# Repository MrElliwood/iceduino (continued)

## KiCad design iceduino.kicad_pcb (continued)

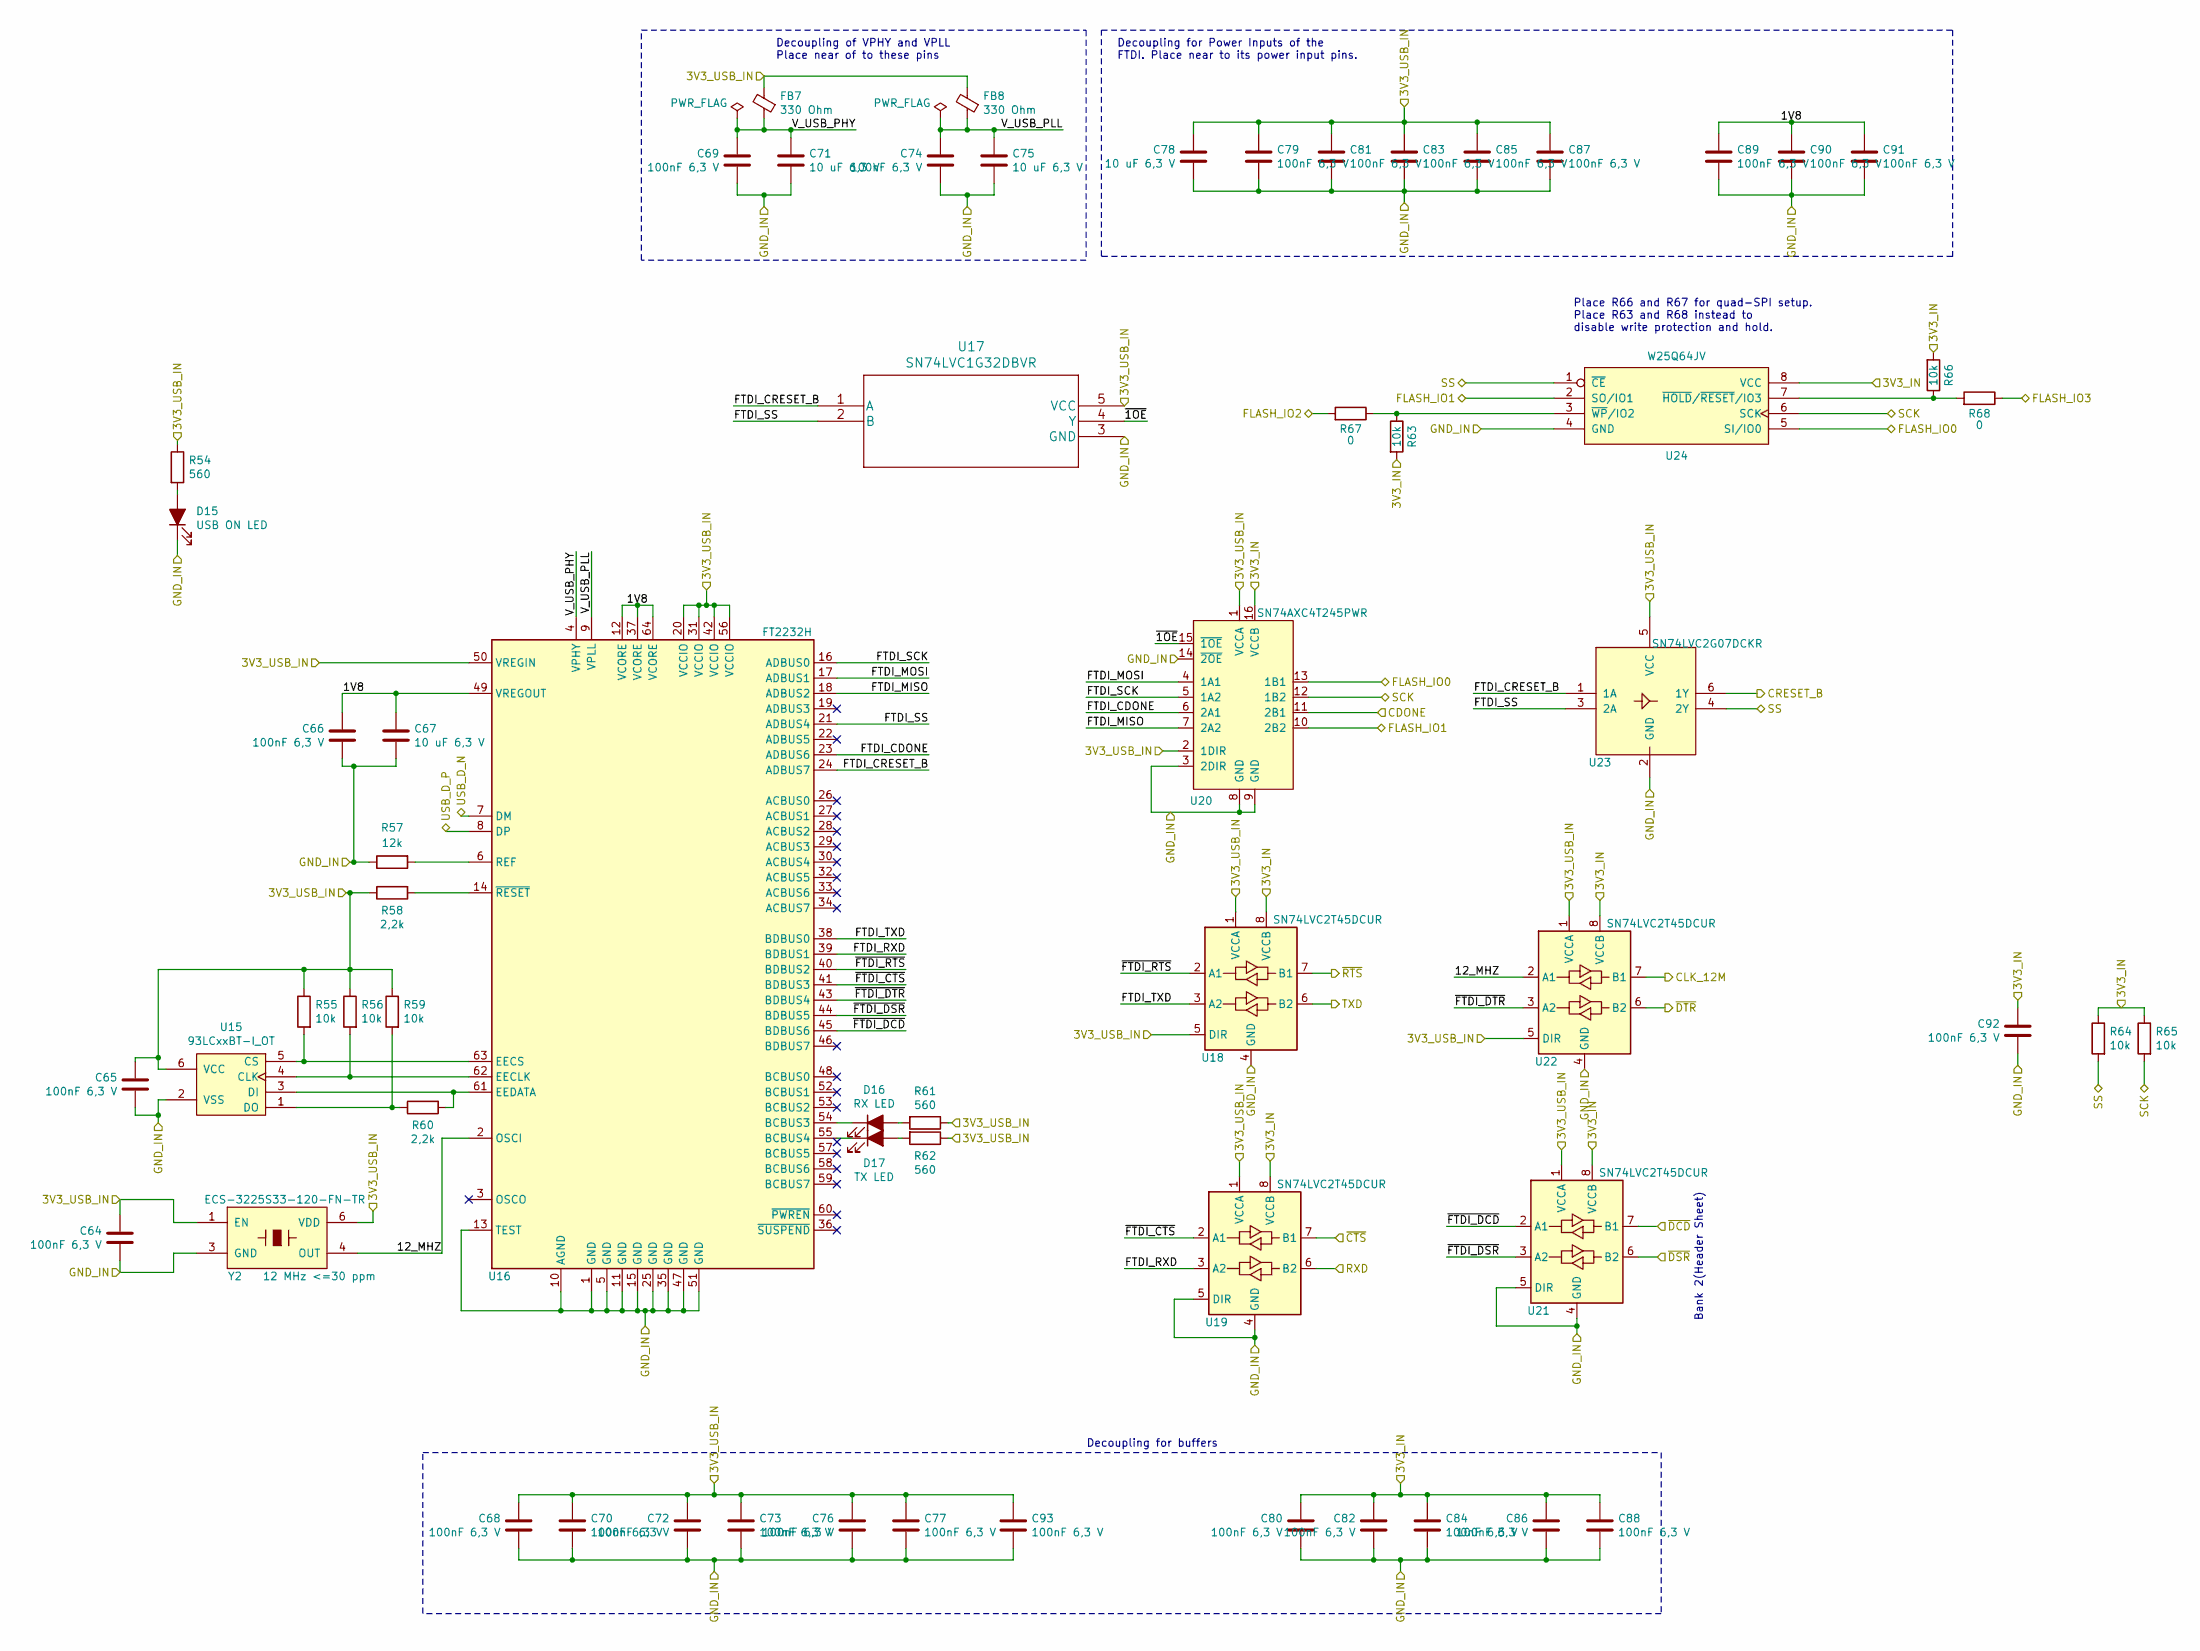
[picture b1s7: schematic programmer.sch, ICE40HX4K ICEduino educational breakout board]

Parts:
C64, C65, C66, C68, C69, C70, C72, C73, C74, C76, C77, C79, C80, C81, C82, C83, C84, C85, C86, C87, C88, C89, C90, C91, C92, C93: 100nF 6,3 V; C_0603_1608Metric; Mfg Part Num CL10B104KB8NNNC; Digikey 1276-1000-1-ND
C67, C71, C75, C78: 10 uF 6,3 V; C_0603_1608Metric; Mfg Part Num CL10A106MQ8NNNC; Digikey 1276-1119-1-ND
D15: USB ON LED; LED_0603_1608Metric; Mfg Part Num SML-D12U1WT86; Digikey SML-D12U1WT86CT-ND
D16: RX LED; LED_0603_1608Metric; Mfg Part Num SML-D12U1WT86; Digikey SML-D12U1WT86CT-ND
D17: TX LED; LED_0603_1608Metric; Mfg Part Num SML-D12U1WT86; Digikey SML-D12U1WT86CT-ND
FB7, FB8: 330 Ohm; R_0805_2012Metric; Mfg Part Num MPZ2012S331AT000; Digikey 445-1569-1-ND
R54, R61, R62: 560; R_0603_1608Metric; Mfg Part Num RK73B1JTTD561J; Digikey 2019-RK73B1JTTD561JCT-ND
R55, R56, R59, R63, R64, R65, R66: 10k; R_0603_1608Metric; Mfg Part Num RMCF0603JT10K0; Digikey RMCF0603JT10K0CT-ND
R57: 12k; R_0603_1608Metric; Mfg Part Num RC0603JR-0712KL; Digikey 311-12KGRCT-ND
R58, R60: 2,2k; R_0603_1608Metric; Mfg Part Num RC0603FR-072K2L; Digikey 311-2.20KHRCT-ND
R67, R68: 0; R_0603_1608Metric
U15: 93LCxxBT-I_OT; SOT-23-6; Mfg Part Num 93LC56BT-I/OT; Digikey 93LC56BT-I/OTCT-ND
U16: FT2232H; LQFP-64_10x10mm_P0.5mm; Mfg Part Num FT2232HL-REEL; Digikey 768-1024-1-ND
U17: SN74LVC1G32DBVR; SOT-23-5; Mfg Part Num SN74LVC1G32DBVR; Digikey 296-9847-1-ND
U18, U19, U21, U22: SN74LVC2T45DCUR; VSSOP-8_2.4x2.1mm_P0.5mm; Mfg Part Num SN74LVC2T45DCUR; Digikey 296-17014-1-ND
U20: SN74AXC4T245PWR; TSSOP-16_4.4x5mm_P0.65mm; Mfg Part Num SN74AXC4T245PWR; Digikey 296-53472-1-ND
U23: SN74LVC2G07DCKR; SOT-363_SC-70-6; Mfg Part Num SN74LVC2G07DCKR; Digikey 296-13495-1-ND
U24: W25Q64JV; SOIC-8_5.23x5.23mm_P1.27mm; Mfg Part Num W25Q64JVSSIM TR; Digikey W25Q64JVSSIMCT-ND
Y2: ECS-3225S33-120-FN-TR; Y_ECS-3225S_3.2x2.5mm_footprint; Mfg Part Num ECS-3225S33-120-FN-TR; Digikey XC2217CT-ND

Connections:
+3V3: C80.1, C82.1, C84.1, C86.1, C88.1, C92.1, R63.2, R64.1, R65.1, R66.2, U18.8 (VCCB), U19.8 (VCCB), U20.16 (VCCB), U21.8 (VCCB), U22.8 (VCCB), U24.8 (VCC); also elsewhere on the board
+3V3_FTDI: C64.1, C65.1, C68.1, C70.1, C72.1, C73.1, C76.1, C77.1, C78.1, C79.1, C81.1, C83.1, C85.1, C87.1, C93.1, FB7.2, FB8.2, R54.1, R55.1, R56.1, R58.1, R59.1, R61.1, R62.1, U15.6 (VCC), U16.20 (VCCIO), U16.31 (VCCIO), U16.42 (VCCIO), U16.50 (VREGIN), U16.56 (VCCIO), U17.5 (VCC), U18.1 (VCCA), U18.5 (DIR), U19.1 (VCCA), U20.1 (VCCA), U20.2 (1DIR), U21.1 (VCCA), U22.1 (VCCA), U22.5 (DIR), U23.5 (VCC), Y2.1 (EN), Y2.6 (VDD); also elsewhere on the board
/CDONE: U20.11 (2B1); also elsewhere on the board
/CLK_12M: U22.7 (B1); also elsewhere on the board
/CRESET_B: U23.6 (1Y); also elsewhere on the board
/FLASH_IO0: U20.13 (1B1), U24.5 (SI/IO0); also elsewhere on the board
/FLASH_IO1: U20.10 (2B2), U24.2 (SO/IO1); also elsewhere on the board
/FLASH_IO2: R67.2; also elsewhere on the board
/FLASH_IO3: R68.1; also elsewhere on the board
/RXD: U19.6 (B2); also elsewhere on the board
/SCK: R65.2, U20.12 (1B2), U24.6 (SCK); also elsewhere on the board
/SS: R64.2, U23.4 (2Y), U24.1 (~CE~); also elsewhere on the board
/TXD: U18.6 (B2); also elsewhere on the board
/USB_D_N: U16.7 (DM); also elsewhere on the board
/USB_D_P: U16.8 (DP); also elsewhere on the board
/USB_PROGRAMMER/1V8: C66.1, C67.1, C89.1, C90.1, C91.1, U16.12 (VCORE), U16.37 (VCORE), U16.49 (VREGOUT), U16.64 (VCORE)
/USB_PROGRAMMER/12_MHZ: U16.2 (OSCI), U22.2 (A1), Y2.4 (OUT)
/USB_PROGRAMMER/FTDI_CDONE: U16.23 (ADBUS6), U20.6 (2A1)
/USB_PROGRAMMER/FTDI_CRESET_B: U16.24 (ADBUS7), U17.1 (A), U23.1 (1A)
/USB_PROGRAMMER/FTDI_MISO: U16.18 (ADBUS2), U20.7 (2A2)
/USB_PROGRAMMER/FTDI_MOSI: U16.17 (ADBUS1), U20.4 (1A1)
/USB_PROGRAMMER/FTDI_RXD: U16.39 (BDBUS1), U19.3 (A2)
/USB_PROGRAMMER/FTDI_SCK: U16.16 (ADBUS0), U20.5 (1A2)
/USB_PROGRAMMER/FTDI_SS: U16.21 (ADBUS4), U17.2 (B), U23.3 (2A)
/USB_PROGRAMMER/FTDI_TXD: U16.38 (BDBUS0), U18.3 (A2)
/USB_PROGRAMMER/V_USB_PHY: C69.1, C71.1, FB7.1, U16.4 (VPHY)
/USB_PROGRAMMER/V_USB_PLL: C74.1, C75.1, FB8.1, U16.9 (VPLL)
/USB_PROGRAMMER/~1OE~: U17.4 (Y), U20.15 (~1OE~)
/USB_PROGRAMMER/~FTDI_CTS~: U16.41 (BDBUS3), U19.2 (A1)
/USB_PROGRAMMER/~FTDI_DCD~: U16.45 (BDBUS6), U21.2 (A1)
/USB_PROGRAMMER/~FTDI_DSR~: U16.44 (BDBUS5), U21.3 (A2)
/USB_PROGRAMMER/~FTDI_DTR~: U16.43 (BDBUS4), U22.3 (A2)
/USB_PROGRAMMER/~FTDI_RTS~: U16.40 (BDBUS2), U18.2 (A1)
/~CTS~: U19.7 (B1); also elsewhere on the board
/~DCD~: U21.7 (B1); also elsewhere on the board
/~DSR~: U21.6 (B2); also elsewhere on the board
/~DTR~: U22.6 (B2); also elsewhere on the board
/~RTS~: U18.7 (B1); also elsewhere on the board
GND: C64.2, C65.2, C66.2, C67.2, C68.2, C69.2, C70.2, C71.2, C72.2, C73.2, C74.2, C75.2, C76.2, C77.2, C78.2, C79.2, C80.2, C81.2, C82.2, C83.2, C84.2, C85.2, C86.2, C87.2, C88.2, C89.2, C90.2, C91.2, C92.2, C93.2, D15.1 (K), R57.1, U15.2 (VSS), U16.1 (GND), U16.5 (GND), U16.10 (AGND), U16.11 (GND), U16.13 (TEST), U16.15 (GND), U16.25 (GND), U16.35 (GND), U16.47 (GND), U16.51 (GND), U17.3 (GND), U18.4 (GND), U19.4 (GND), U19.5 (DIR), U20.3 (2DIR), U20.8 (GND), U20.9 (GND), U20.14 (~2OE~), U21.4 (GND), U21.5 (DIR), U22.4 (GND), U23.2 (GND), U24.4 (GND), Y2.3 (GND); also elsewhere on the board
unnamed: D15.2 (A), R54.2
unnamed: D16.1 (K), U16.54 (BCBUS3)
unnamed: D16.2 (A), R61.2
unnamed: D17.1 (K), U16.55 (BCBUS4)
unnamed: D17.2 (A), R62.2
unnamed: R55.2, U15.5 (CS), U16.63 (EECS)
unnamed: R56.2, U15.4 (CLK), U16.62 (EECLK)
unnamed: R57.2, U16.6 (REF)
unnamed: R58.2, U16.14 (~RESET)
unnamed: R59.2, R60.1, U15.1 (DO)
unnamed: R60.2, U15.3 (DI), U16.61 (EEDATA)
unnamed: R63.1, R67.1, U24.3 (~WP~/IO2)
unnamed: R66.1, R68.2, U24.7 (~HOLD~/~RESET~/IO3)

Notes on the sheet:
Decoupling of VPHY and VPLL Place near of to these pins
Bank 2(Header Sheet)
Decoupling for Power Inputs of the FTDI. Place near to its power input pins.
Decoupling for buffers
Place R66 and R67 for quad-SPI setup. Place R63 and R68 instead to disable write protection and hold.

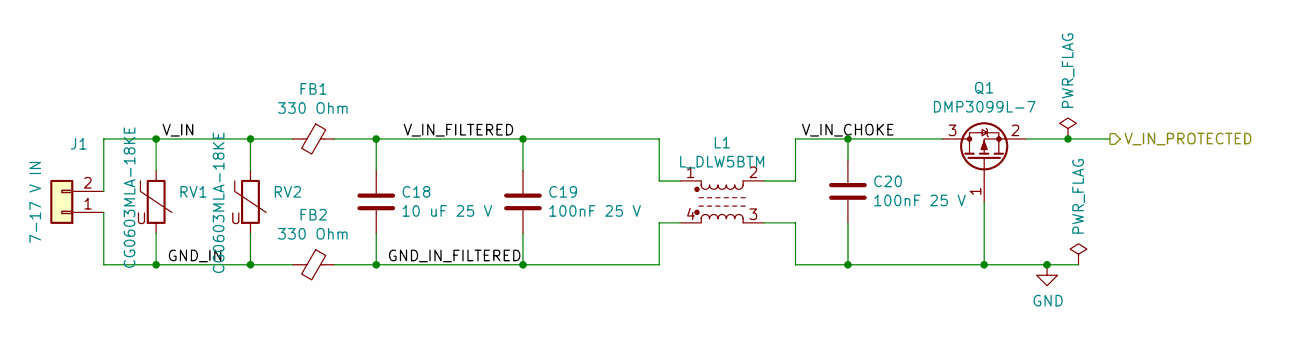
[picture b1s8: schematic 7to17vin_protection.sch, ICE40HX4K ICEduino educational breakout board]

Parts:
C18: 10 uF 25 V; C_0805_2012Metric; Mfg Part Num CL21A106KAYNNNE; Digikey 1276-2891-1-ND
C19, C20: 100nF 25 V; C_0603_1608Metric; Mfg Part Num CL10B104KB8NNNC; Digikey 1276-1000-1-ND
FB1, FB2: 330 Ohm; R_0805_2012Metric; Mfg Part Num MPZ2012S331AT000; Digikey 445-1569-1-ND
J1: 7-17 V IN; TerminalBlock_bornier-2_P5.08mm; Mfg Part Num TB007-508-02BE; Digikey 102-6203-ND
L1: L_DLW5BTM; L_Murata_DLW5BTM_5.00x5.00mm_footprint; Mfg Part Num DLW5BTM251SQ2L; Digikey 490-11111-1-ND
Q1: DMP3099L-7; SOT-23; Mfg Part Num DMP3099L-7; Digikey DMP3099L-7DICT-ND
RV1, RV2: CG0603MLA-18KE; R_0603_1608Metric; Mfg Part Num CG0603MLA-18KE; Digikey CG0603MLA-18KECT-ND

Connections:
/Power/7-17VIN_PROTECTION/GND_IN: FB2.2, J1.1, RV1.2, RV2.2
/Power/7-17VIN_PROTECTION/GND_IN_FILTERED: C18.2, C19.2, FB2.1, L1.4
/Power/7-17VIN_PROTECTION/V_IN: FB1.2, J1.2, RV1.1, RV2.1
/Power/7-17VIN_PROTECTION/V_IN_CHOKE: C20.1, L1.2, Q1.3 (D)
/Power/7-17VIN_PROTECTION/V_IN_FILTERED: C18.1, C19.1, FB1.1, L1.1
/V_IN_PROTECTED: Q1.2 (S); also elsewhere on the board
GND: C20.2, L1.3, Q1.1 (G); also elsewhere on the board

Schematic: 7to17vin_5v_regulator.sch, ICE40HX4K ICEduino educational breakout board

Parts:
C21, C22: 10 uF 25 V; C_0805_2012Metric; Mfg Part Num CL21A106KAYNNNE; Digikey 1276-2891-1-ND
C23: 100nF 25 V; C_0603_1608Metric; Mfg Part Num CL10B104KB8NNNC; Digikey 1276-1000-1-ND
C24: 100nF 6,3 V; C_0603_1608Metric; Mfg Part Num CL10B104KB8NNNC; Digikey 1276-1000-1-ND
C25, C26: 22 uF 6,3 V; C_0603_1608Metric; Mfg Part Num GRM188R60J226MEA0D; Digikey 490-7611-1-ND
C27: 10pF 6,3 V; C_0603_1608Metric; Mfg Part Num CL10C100JB8NNNC; Digikey 1276-1027-1-ND
L2: 4,7 uH; L_Taiyo-Yuden_NR-50xx; Mfg Part Num NR5040T4R7N; Digikey 587-2373-1-ND
R6: 54k9 1%; R_0603_1608Metric; Mfg Part Num RC0603FR-0754K9L; Digikey 311-54.9KHRCT-ND
R7: 10k 1%; R_0603_1608Metric; Mfg Part Num RC0603FR-0710KL; Digikey 311-10.0KHRCT-ND
U3: TPS562201; SOT-23-6; Mfg Part Num TPS562201DDCR; Digikey 296-44397-1-ND
U4, U5: MAX40200AUK; SOT-23-5; Mfg Part Num MAX40200AUK+T; Digikey MAX40200AUK+TCT-ND

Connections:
+5V: U4.5 (OUT), U5.5 (OUT); also elsewhere on the board
/Power/7-17VIN-5V_REGULATOR/5V_IN: C25.1, C26.1, C27.1, L2.2, R6.1, U4.1 (VDD), U4.3 (EN), U5.1 (VDD), U5.3 (EN)
/Power/7-17VIN-5V_REGULATOR/FB_5V: C27.2, R6.2, R7.1, U3.4 (VFB)
/Power/EN_HIGH_VOLTAGE: U3.5 (EN); also elsewhere on the board
/V_IN_PROTECTED: C21.1, C22.1, C23.1, U3.3 (VIN); also elsewhere on the board
GND: C21.2, C22.2, C23.2, C25.2, C26.2, R7.2, U3.1 (GND), U4.2 (GND), U5.2 (GND); also elsewhere on the board
unnamed: C24.1, L2.1, U3.2 (SW)
unnamed: C24.2, U3.6 (VBST)

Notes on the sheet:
5V 2A

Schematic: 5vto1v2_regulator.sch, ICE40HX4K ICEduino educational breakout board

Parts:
C28, C29, C30, C32: 10 uF 6,3 V; C_0603_1608Metric; Mfg Part Num CL10A106MQ8NNNC; Digikey 1276-1119-1-ND
C31: 10pF 6,3 V; C_0603_1608Metric; Mfg Part Num CL10C100JB8NNNC; Digikey 1276-1027-1-ND
L3: 1uH; L_1008_2520Metric_2.5x2mm_footprint; Mfg Part Num MAMK2520T1R0M; Digikey 587-3225-1-ND
R8, R9: 100k 1%; R_0603_1608Metric; Mfg Part Num RC0603FR-07100KL; Digikey 311-100KHRCT-ND
R10: 0; R_0805_2012Metric; Mfg Part Num RC0805JR-070RL; Digikey 311-0.0ARCT-ND
U6: TLV62568APDRLR; Texas_DRL_SOT-563_1.6x1.6mm_0.5mm-pitch_footprint; Mfg Part Num TLV62568APDRLR; Digikey 296-51691-1-ND

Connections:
+1V2: C32.1, R10.1; also elsewhere on the board
+5V: C28.1, U6.3 (VIN); also elsewhere on the board
/CRESET_B: U6.6 (PG); also elsewhere on the board
/Power/5V_1V2_REGULATOR/1V2_REG: C29.1, C30.1, C31.1, L3.2, R8.1, R10.2
/Power/5V_1V2_REGULATOR/FB_1V2: C31.2, R8.2, R9.1, U6.1 (FB)
/Power/EN_LOW_VOLTAGE: U6.5 (EN); also elsewhere on the board
GND: C28.2, C29.2, C30.2, C32.2, R9.2, U6.2 (GND); also elsewhere on the board
unnamed: L3.1, U6.4 (SW)

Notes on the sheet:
In case of noise in the 1.2 V net, replace this resistor R30 with an inductor or an ferrite bead
1,2 V 1 A

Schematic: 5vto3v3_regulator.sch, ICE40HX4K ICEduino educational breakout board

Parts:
C33, C34, C35: 10 uF 6,3 V; C_0603_1608Metric; Mfg Part Num CL10A106MQ8NNNC; Digikey 1276-1119-1-ND
C36: 10pF 6,3 V; C_0603_1608Metric; Mfg Part Num CL10C100JB8NNNC; Digikey 1276-1027-1-ND
D12: LED_ALT; LED_0603_1608Metric; Mfg Part Num SML-D12U1WT86; Digikey SML-D12U1WT86CT-ND
L4: 1uH; L_1008_2520Metric_2.5x2mm_footprint; Mfg Part Num MAMK2520T1R0M; Digikey 587-3225-1-ND
R11: 220k 1%; R_0603_1608Metric; Mfg Part Num RC0603FR-07220KL; Digikey 311-220KHRCT-ND
R12: 48,7k 1%; R_0603_1608Metric; Mfg Part Num RC0603FR-0748K7L; Digikey 311-48.7KHRCT-ND
R13: 10k; R_0603_1608Metric; Mfg Part Num RMCF0603JT10K0; Digikey RMCF0603JT10K0CT-ND
R14: 560; R_0603_1608Metric; Mfg Part Num RK73B1JTTD561J; Digikey 2019-RK73B1JTTD561JCT-ND
U7: TLV62568APDRLR; Texas_DRL_SOT-563_1.6x1.6mm_0.5mm-pitch_footprint; Mfg Part Num TLV62568APDRLR; Digikey 296-51691-1-ND

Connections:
+3V3: C34.1, C35.1, C36.1, L4.2, R11.1, R13.1, R14.1; also elsewhere on the board
+5V: C33.1, U7.3 (VIN); also elsewhere on the board
/CRESET_B: R13.2, U7.6 (PG); also elsewhere on the board
/Power/5V_3V3_REGULATOR/FB_3V3: C36.2, R11.2, R12.1, U7.1 (FB)
/Power/EN_LOW_VOLTAGE: U7.5 (EN); also elsewhere on the board
GND: C33.2, C34.2, C35.2, D12.1 (K), R12.2, U7.2 (GND); also elsewhere on the board
unnamed: D12.2 (A), R14.2
unnamed: L4.1, U7.4 (SW)

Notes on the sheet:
3,3 V 1 A
Note: Use TLV62568ADRLR for 2 A

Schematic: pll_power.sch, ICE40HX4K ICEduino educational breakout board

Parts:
C37, C39: 10 uF 6,3 V; C_0603_1608Metric; Mfg Part Num CL10A106MQ8NNNC; Digikey 1276-1119-1-ND
C38, C40: 100nF 6,3 V; C_0603_1608Metric; Mfg Part Num CL10B104KB8NNNC; Digikey 1276-1000-1-ND
R15, R16: 100; R_0603_1608Metric; Mfg Part Num RMCF0603FT100R; Digikey RMCF0603FT100RCT-ND

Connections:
+1V2: R15.1, R16.1; also elsewhere on the board
/GNDPLL_0: C37.2, C38.2; also elsewhere on the board
/GNDPLL_1: C39.2, C40.2; also elsewhere on the board
/VCCPLL_0: C37.1, C38.1, R15.2; also elsewhere on the board
/VCCPLL_1: C39.1, C40.1, R16.2; also elsewhere on the board

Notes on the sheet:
Power for PLLs GND must not be connected to Board Ground

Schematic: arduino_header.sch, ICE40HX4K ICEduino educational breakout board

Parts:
J3, J6: Conn_01x08; PinSocket_1x08_P2.54mm_Vertical; Mfg Part Num PPPC081LFBN-RC; Digikey S7041-ND
J4: Conn_01x06; PinSocket_1x06_P2.54mm_Vertical; Mfg Part Num PPPC061LFBN-RC; Digikey S7039-ND
J5: Conn_01x10; PinSocket_1x10_P2.54mm_Vertical; Mfg Part Num 61301011821; Digikey 732-2859-ND

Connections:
+5V: J3.2, J3.5; also elsewhere on the board
/HEADER/INO_3V3: J3.4; also elsewhere on the board
/HEADER/INO_A0: J4.1; also elsewhere on the board
/HEADER/INO_A1: J4.2; also elsewhere on the board
/HEADER/INO_A2: J4.3; also elsewhere on the board
/HEADER/INO_A3: J4.4; also elsewhere on the board
/HEADER/INO_A4: J4.5; also elsewhere on the board
/HEADER/INO_A5: J4.6; also elsewhere on the board
/HEADER/INO_AREF: J5.3; also elsewhere on the board
/HEADER/INO_D2: J6.6; also elsewhere on the board
/HEADER/INO_D3: J6.5; also elsewhere on the board
/HEADER/INO_D4: J6.4; also elsewhere on the board
/HEADER/INO_D5: J6.3; also elsewhere on the board
/HEADER/INO_D6: J6.2; also elsewhere on the board
/HEADER/INO_D7: J6.1; also elsewhere on the board
/HEADER/INO_D8: J5.10; also elsewhere on the board
/HEADER/INO_D9: J5.9; also elsewhere on the board
/HEADER/INO_MISO: J5.6; also elsewhere on the board
/HEADER/INO_MOSI: J5.7; also elsewhere on the board
/HEADER/INO_RX: J6.8; also elsewhere on the board
/HEADER/INO_SCK: J5.5; also elsewhere on the board
/HEADER/INO_SCL: J5.1; also elsewhere on the board
/HEADER/INO_SDA: J5.2; also elsewhere on the board
/HEADER/INO_SS: J5.8; also elsewhere on the board
/HEADER/INO_TX: J6.7; also elsewhere on the board
/INO_RESET: J3.3; also elsewhere on the board
GND: J3.6, J3.7, J5.4; also elsewhere on the board

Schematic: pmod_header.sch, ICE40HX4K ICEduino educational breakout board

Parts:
PMOD1, PMOD2, PMOD3: Conn_02x06_Odd_Even; PinSocket_2x06_P2.54mm_Horizontal; Mfg Part Num PPPC062LJBN-RC; Digikey S5559-ND

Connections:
/HEADER/PMOD_3V3: PMOD1.1, PMOD1.2, PMOD2.1, PMOD2.2, PMOD3.1, PMOD3.2; also elsewhere on the board
/P1_1: PMOD1.11; also elsewhere on the board
/P1_2: PMOD2.11; also elsewhere on the board
/P1_3: PMOD3.11; also elsewhere on the board
/P2_1: PMOD1.9; also elsewhere on the board
/P2_2: PMOD2.9; also elsewhere on the board
/P2_3: PMOD3.9; also elsewhere on the board
/P3_1: PMOD1.7; also elsewhere on the board
/P3_2: PMOD2.7; also elsewhere on the board
/P3_3: PMOD3.7; also elsewhere on the board
/P4_1: PMOD1.5; also elsewhere on the board
/P4_2: PMOD2.5; also elsewhere on the board
/P4_3: PMOD3.5; also elsewhere on the board
/P7_1: PMOD1.12; also elsewhere on the board
/P7_2: PMOD2.12; also elsewhere on the board
/P7_3: PMOD3.12; also elsewhere on the board
/P8_1: PMOD1.10; also elsewhere on the board
/P8_2: PMOD2.10; also elsewhere on the board
/P8_3: PMOD3.10; also elsewhere on the board
/P9_1: PMOD1.8; also elsewhere on the board
/P9_2: PMOD2.8; also elsewhere on the board
/P9_3: PMOD3.8; also elsewhere on the board
/P10_1: PMOD1.6; also elsewhere on the board
/P10_2: PMOD2.6; also elsewhere on the board
/P10_3: PMOD3.6; also elsewhere on the board
GND: PMOD1.3, PMOD1.4, PMOD2.3, PMOD2.4, PMOD3.3, PMOD3.4; also elsewhere on the board

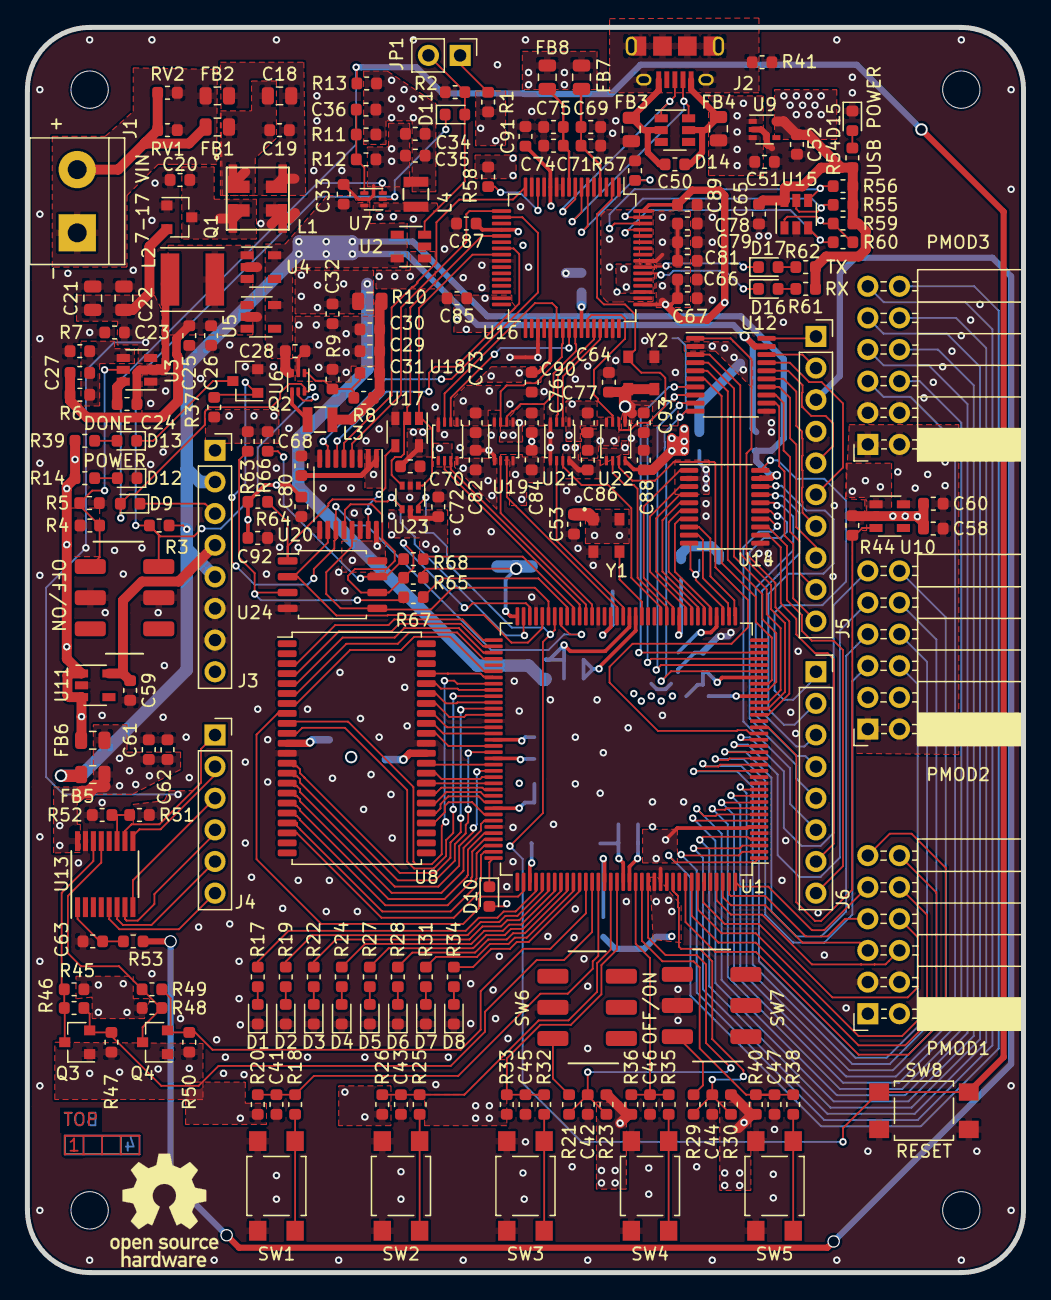
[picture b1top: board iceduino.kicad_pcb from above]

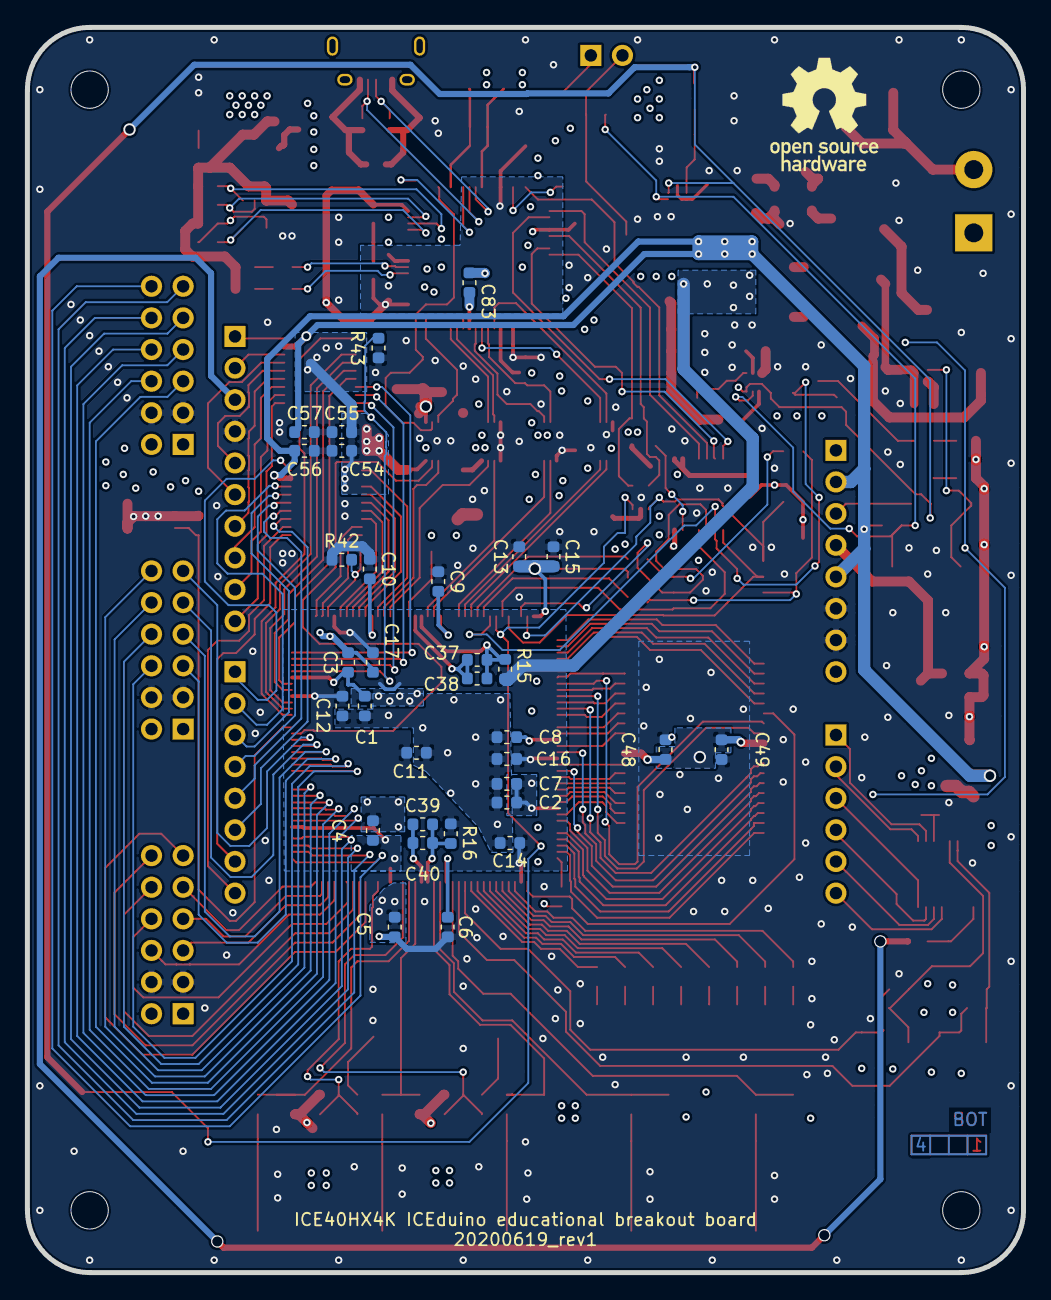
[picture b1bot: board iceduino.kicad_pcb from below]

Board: 4 copper layers, 80.0 x 100.0 mm, 245 parts (32 on the bottom side), 223 nets.

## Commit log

2020-05-27 Cleanup
2020-05-27 new project
2020-05-27 7-17VIN Power
2020-05-27 Voltage Regulators
2020-05-27 ui sheet
2020-06-12 Schematic modified (Hierarchy) Bug where SPI was active when creset or ss was low fixed PCB layout started (almost all parts are at position) No parts on the bottom so far Arduino and PMOD header spa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
2020-06-13 8MBit Flash swapped to a 64MBit one
2020-06-15 Added wires for quad-SPI Flash operation
2020-06-15 7-17 VIN Power PIN Header moved to the left for better compatibility with extension boards. Added 0 Ohm resistors for optional desoldering of quad-SPI wires. USB power jumper moved more to the side o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
2020-06-15 Move of decoupling capacitors from last commit reverted (meant for Arduino Header Level Shifters). Component placement complete.
2020-06-16 FPGA PINs for PMOD reorganized FPGA PINs for Arduino Header reorganized Trace routing partially ready
2020-06-18 Oscillator Footprints bug fixed in the footprint library
2020-06-18 Board design completed Revision 1
2020-06-19 Added project description in kicad schematic sheets Added project name and OSHW logo on the board
2020-06-19 Bigger OSHW logo
2020-06-19 Power layer was not entirely used
2020-06-19 Gerber and Drill Files
2020-06-19 Power layer still wasn't entirely used
2020-06-19 Bill of materials
2020-06-19 Part specifications added to the VBUS Enable Jumper
2020-08-12 Schaltpläne als pdf und svg
